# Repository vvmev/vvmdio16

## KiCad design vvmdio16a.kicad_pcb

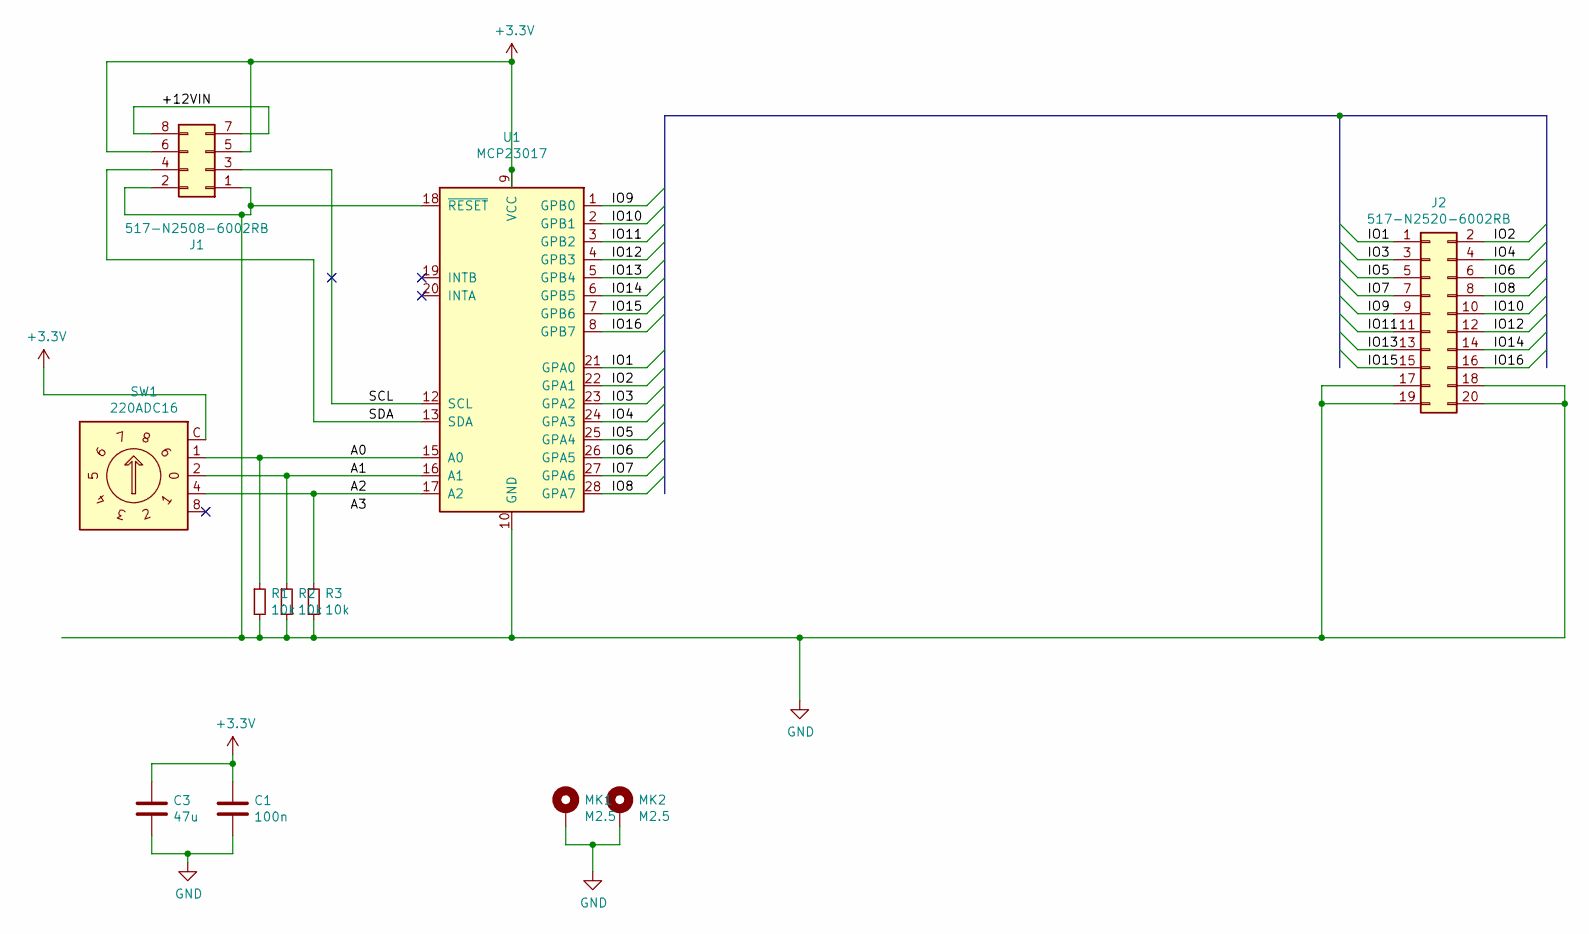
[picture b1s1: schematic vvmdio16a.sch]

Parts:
C1: 100n; C_0805_HandSoldering
C3: 47u; C_0805_HandSoldering
J1: 517-N2508-6002RB; IDC-Header_2x04_P2.54mm_Vertical
J2: 517-N2520-6002RB; IDC-Header_2x10_Pitch2.54mm_Straight
MK1, MK2: M2.5; MountingHole_2.7mm_M2.5_DIN965_Pad
R1, R2, R3: 10k; R_0805_HandSoldering
SW1: 220ADC16; Nidec_Copal_SH-7010C
U1: MCP23017; SOIC-28W_7.5x18.7mm_Pitch1.27mm

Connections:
+3V3: C1.1, C3.1, J1.5, J1.6, SW1.C, U1.9 (VCC)
/+12VIN: J1.7, J1.8
/A0: R1.1, SW1.1, U1.15 (A0)
/A1: R2.1, SW1.2, U1.16 (A1)
/A2: R3.1, SW1.4, U1.17 (A2)
/IO1: J2.1, U1.21 (GPA0)
/IO2: J2.2, U1.22 (GPA1)
/IO3: J2.3, U1.23 (GPA2)
/IO4: J2.4, U1.24 (GPA3)
/IO5: J2.5, U1.25 (GPA4)
/IO6: J2.6, U1.26 (GPA5)
/IO7: J2.7, U1.27 (GPA6)
/IO8: J2.8, U1.28 (GPA7)
/IO9: J2.9, U1.1 (GPB0)
/IO10: J2.10, U1.2 (GPB1)
/IO11: J2.11, U1.3 (GPB2)
/IO12: J2.12, U1.4 (GPB3)
/IO13: J2.13, U1.5 (GPB4)
/IO14: J2.14, U1.6 (GPB5)
/IO15: J2.15, U1.7 (GPB6)
/IO16: J2.16, U1.8 (GPB7)
/SCL: J1.3, U1.12 (SCL)
/SDA: J1.4, U1.13 (SDA)
GND: C1.2, C3.2, J1.1, J1.2, J2.17, J2.18, J2.19, J2.20, MK1.1, MK2.1, R1.2, R2.2, R3.2, U1.10 (GND), U1.18 (~RESET)

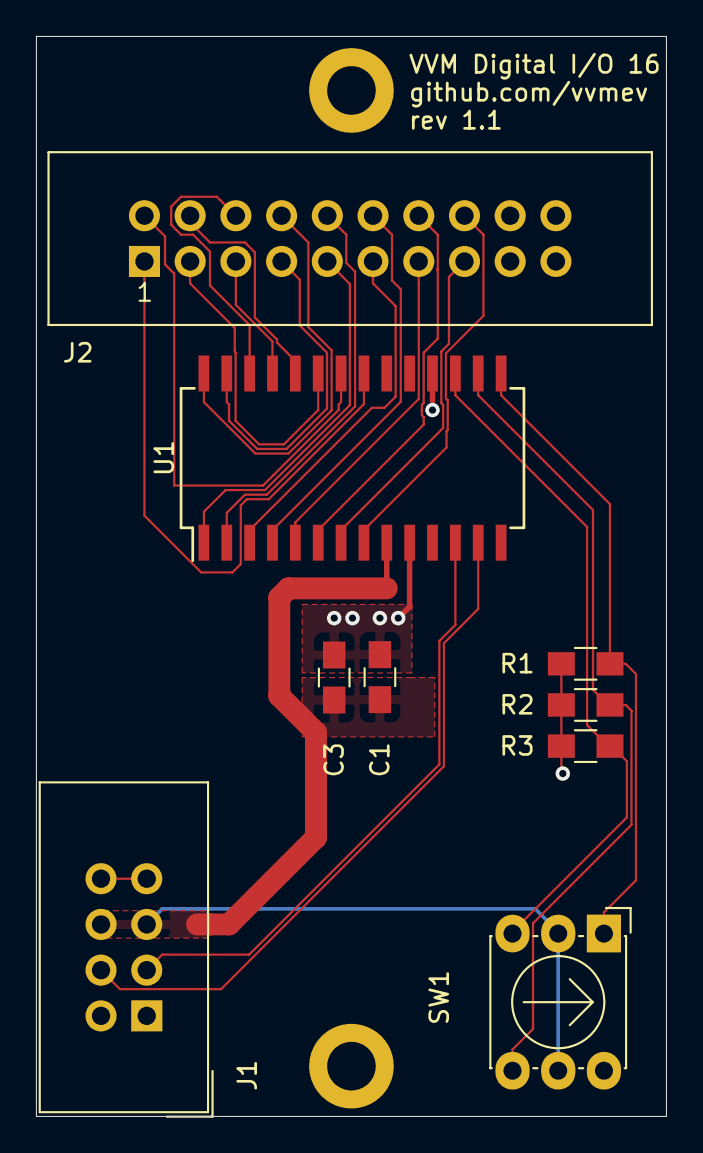
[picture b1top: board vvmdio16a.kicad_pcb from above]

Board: 2 copper layers, 35.0 x 60.0 mm, 11 parts (0 on the bottom side), 24 nets.

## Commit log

2019-05-02 CYOP vvmdo16 and replace with 27013
2019-05-02 add PDF of schematics
2019-05-05 ready for plotting
2019-05-30 Use correct footprint for IC
